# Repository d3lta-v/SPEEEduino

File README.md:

Designed by MakerFoundry LLP | Designed, assembled and tested in Singapore

# SPEEEduino
SPEEEduino is an easy to use Wi-Fi enabled microcontroller, designed and fabricated by EEE students. Users can write programs to connect or control things over the Internet.

Official Reference Website: [https://sites.google.com/view/speeeduino/home](https://sites.google.com/view/speeeduino/home)

Related project: [ESPblaster](https://github.com/sammy0025/ESPblaster)

## Technical information

### Repository Layout
* **SPEEEduino_v1.0**: EAGLE files for the old SPEEEduino v1.0, which is deprecated
* **SPEEEduino_v1.1**: EAGLE files for thew new SPEEEduino
* **Low Level Library**: The SPEEEduino Low Level Library, which is an Arduino library that provides an easy way to interface with the ESP8266-01 module with the SPEEEduino.
* **docs**: The [github.io homepage](https://sammy0025.github.io/SPEEEduino/) for the SPEEEduino
* **Image Assets**: Image assets for websites related to the SPEEEduino and markdown pages.

### Startup states table
A simplified version of this table is also available on the back of the SPEEEduino v1.1's board.

|  | GPIO0 (1) | GPIO2 (2) | ESP-RX connect to D4 (3) | ESP-TX connect to D2 (4) | ESP-RESET Button |
|---------|:---------:|:---------:|:---------:|:---------:|:---------:|
| Wi-Fi Enable | ⬆️ | ⬆️ | ⬆️ | ⬆️ | Leave open |
| Disconnect ESP-01 | ❎ | ❎ | ⬇️ | ⬇️ | Leave open |
| Reset ESP-01 | ❎ | ❎ | ❎ | ❎ | Press down |
| Flash ESP-01 | ⬇️ | ⬆️ | ⬇️ | ⬇️ | Press down, set switches, release |

## Contributing
Contributing to the SPEEEduino Git Repository requires you to have EAGLE 8.4 or newer which supports Managed Libraries.

SPEEEduino primarily uses EAGLE's Managed Libraries made by Sparkfun, but also contain our own custom footprints and SMD component footprints from Cytron.

## Our team
* Project Supervisor: [Teo Shin Jen](https://www.youracclaim.com/user/sjteo)
* Chief Designer: Pan Ziyue ([@sammy0025](https://twitter.com/sammy0025))
* Assistants/Advisers: Julian Kang ([@Julian_KBK](https://twitter.com/Julian_KBK)), Goh Qian Zhe ([@QianZheGoh](https://twitter.com/QianZheGoh))
* Videographer: [@QianZheGoh](https://twitter.com/QianZheGoh)
* The awesome folks at Arduino, Sparkfun and Adafruit for technical reference and ECAD models.

Open Source Hardware (OSHW)

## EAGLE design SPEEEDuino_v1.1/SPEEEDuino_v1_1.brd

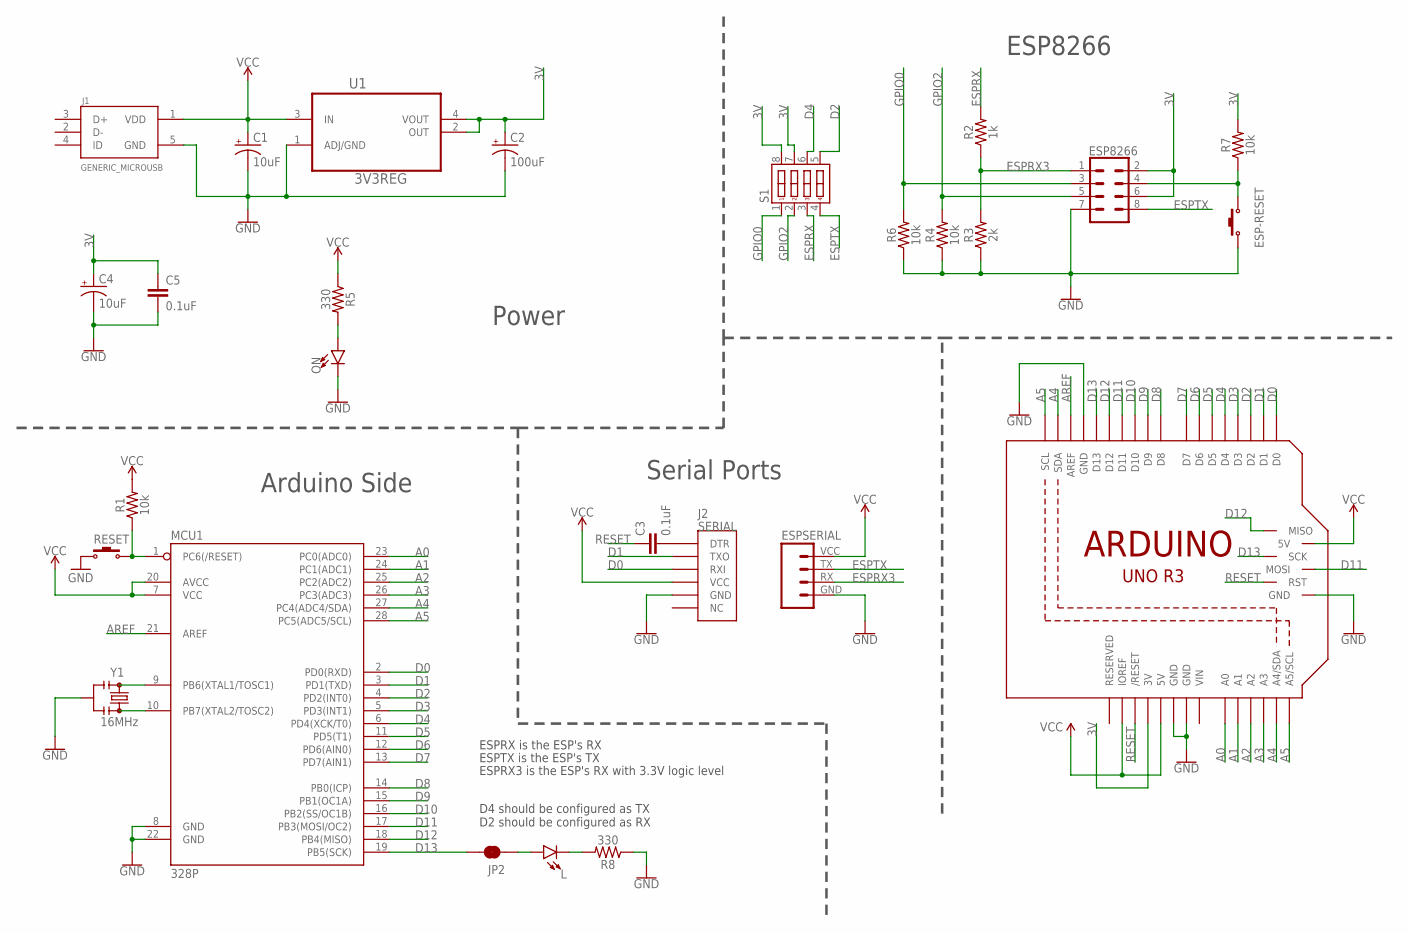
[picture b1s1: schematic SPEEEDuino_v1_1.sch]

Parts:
C1: 10uF; EIA3528
C2: 100uF; PANASONIC_D
C3, C5: 0.1uF; 1206
C4: 10uF; EIA3216
ESP8266: CONN_04X2; 2X4
ESP-RESET: SW-PB_(KAN0641); S-SP-4N-KAN0641
ESPSERIAL: ESP8266-SERIAL0; 1X04
J1: GENERIC_MICROUSB; FRAMATOME_10118194-0001LF
J2: SERIAL; CP2102_DEVICE_SIDE
JP2: JUMPER-SMT_2_NC_TRACE_SILK; SMT-JUMPER_2_NC_TRACE_SILK
L: LED3MM; LED_3MM
M1: ARDUINO_R3_ICSP; ARDUINOR3_ICSP
MCU1: 328P; DIP28
ON: LED3MM; LED_3MM
R1, R4, R6, R7: 10k; 1206
R2: 1k; 1206
R3: 2k; 1206
R5, R8: 330; 1206
RESET: SW-PB_(KAN0641); S-SP-4N-KAN0641
S1: 4 WAYS; SW-DIP-4-SMD
U1: 3V3REG; SOT230P696X180-4N
Y1: 16MHz; RESONATOR-SMD-3.2X1.3

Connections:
3V: C2.+, C4.+, C5.1, ESP8266.2, ESP8266.6, M1.3V, R7.2, S1.7, S1.8, U1.2 (OUT), U1.4 (VOUT)
A0: M1.A0, MCU1.23 (PC0(ADC0))
A1: M1.A1, MCU1.24 (PC1(ADC1))
A2: M1.A2, MCU1.25 (PC2(ADC2))
A3: M1.A3, MCU1.26 (PC3(ADC3))
A4: M1.A4 (A4/SDA), M1.SDA, MCU1.27 (PC4(ADC4/SDA))
A5: M1.A5 (A5/SCL), M1.SCL, MCU1.28 (PC5(ADC5/SCL))
AREF: M1.AREF, MCU1.21 (AREF)
D0: J2.P$3 (RXI), M1.D0, MCU1.2 (PD0(RXD))
D1: J2.P$2 (TXO), M1.D1, MCU1.3 (PD1(TXD))
D2: M1.D2, MCU1.4 (PD2(INT0)), S1.5
D3: M1.D3, MCU1.5 (PD3(INT1))
D4: M1.D4, MCU1.6 (PD4(XCK/T0)), S1.6
D5: M1.D5, MCU1.11 (PD5(T1))
D6: M1.D6, MCU1.12 (PD6(AIN0))
D7: M1.D7, MCU1.13 (PD7(AIN1))
D8: M1.D8, MCU1.14 (PB0(ICP))
D9: M1.D9, MCU1.15 (PB1(OC1A))
D10: M1.D10, MCU1.16 (PB2(SS/OC1B))
D11: M1.D11, M1.MOSI, MCU1.17 (PB3(MOSI/OC2))
D12: M1.D12, M1.MISO, MCU1.18 (PB4(MISO))
D13: JP2.2, M1.D13, M1.SCK, MCU1.19 (PB5(SCK))
DTR: C3.2, J2.P$1 (DTR)
ESPRESET: ESP8266.4, ESP-RESET.3 (2), ESP-RESET.4 (2), R7.1
ESPRX: R2.2, S1.3
ESPRX3: ESP8266.1, ESPSERIAL.RX (TX), R2.1, R3.2
ESPTX: ESP8266.8, ESPSERIAL.TX (RX), S1.4
GND: C1.C (-), C2.-, C4.-, C5.2, ESP8266.7, ESP-RESET.1, ESP-RESET.2 (1), ESPSERIAL.GND (VCC), J1.5 (GND), J2.P$5 (GND), M1.GND, M1.GND@1 (GND), M1.GND@2 (GND), M1.GND@3 (GND), MCU1.8 (GND), MCU1.22 (GND), ON.K (C), R3.1, R4.1, R6.1, R8.1, RESET.1, RESET.2 (1), U1.1 (ADJ/GND), Y1.2
GPIO0: ESP8266.3, R6.2, S1.1
GPIO2: ESP8266.5, R4.2, S1.2
unnamed: MCU1.10 (PB7(XTAL2/TOSC2)), Y1.3
unnamed: L.K (C), R8.2
unnamed: JP2.1, L.A
unnamed: ON.A, R5.2
unnamed: MCU1.9 (PB6(XTAL1/TOSC1)), Y1.1
RESET: C3.1, M1.RESET (/RESET), M1.RESET_ICSP (RST), MCU1.1 (PC6(/RESET)), R1.1, RESET.3 (2), RESET.4 (2)
VCC: C1.A (+), ESPSERIAL.VCC (GND), J1.1 (VDD), J2.P$4 (VCC), M1.5V, M1.5V_ICSP (5V), M1.IOREF, MCU1.7 (VCC), MCU1.20 (AVCC), R1.2, R5.1, U1.3 (IN)
VIN: M1.VIN

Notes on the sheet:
ESPRX is the ESP's RX
ESPTX is the ESP's TX
D4 should be configured as TX D2 should be configured as RX
ESPRX3 is the ESP's RX with 3.3V logic level
Power
Arduino Side
Serial Ports
ESP8266

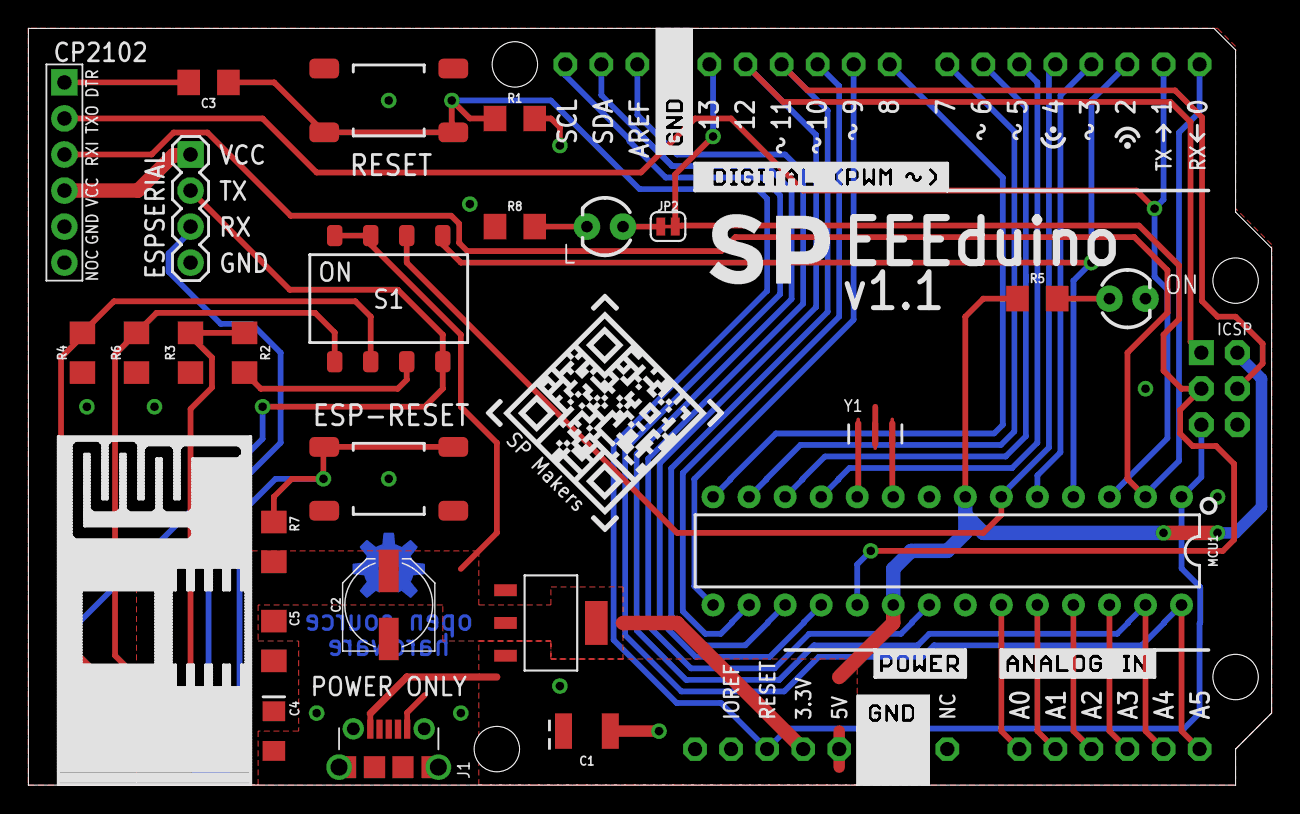
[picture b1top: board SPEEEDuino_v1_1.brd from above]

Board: 2 copper layers, 87.6 x 53.3 mm, 33 parts (0 on the bottom side), 37 nets.

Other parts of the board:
U$1: ESP8266-NEGASILK
U$2: SP-LOGO-BIGGER
U$3: ESP8266-NEGASILK-INV
U$4: OSHW-LOGO-M_COPPER-SOLDERMASK-INV
U$5: MAKERCLUB-QR
U$6: SP-LOGO-SMALL-INV

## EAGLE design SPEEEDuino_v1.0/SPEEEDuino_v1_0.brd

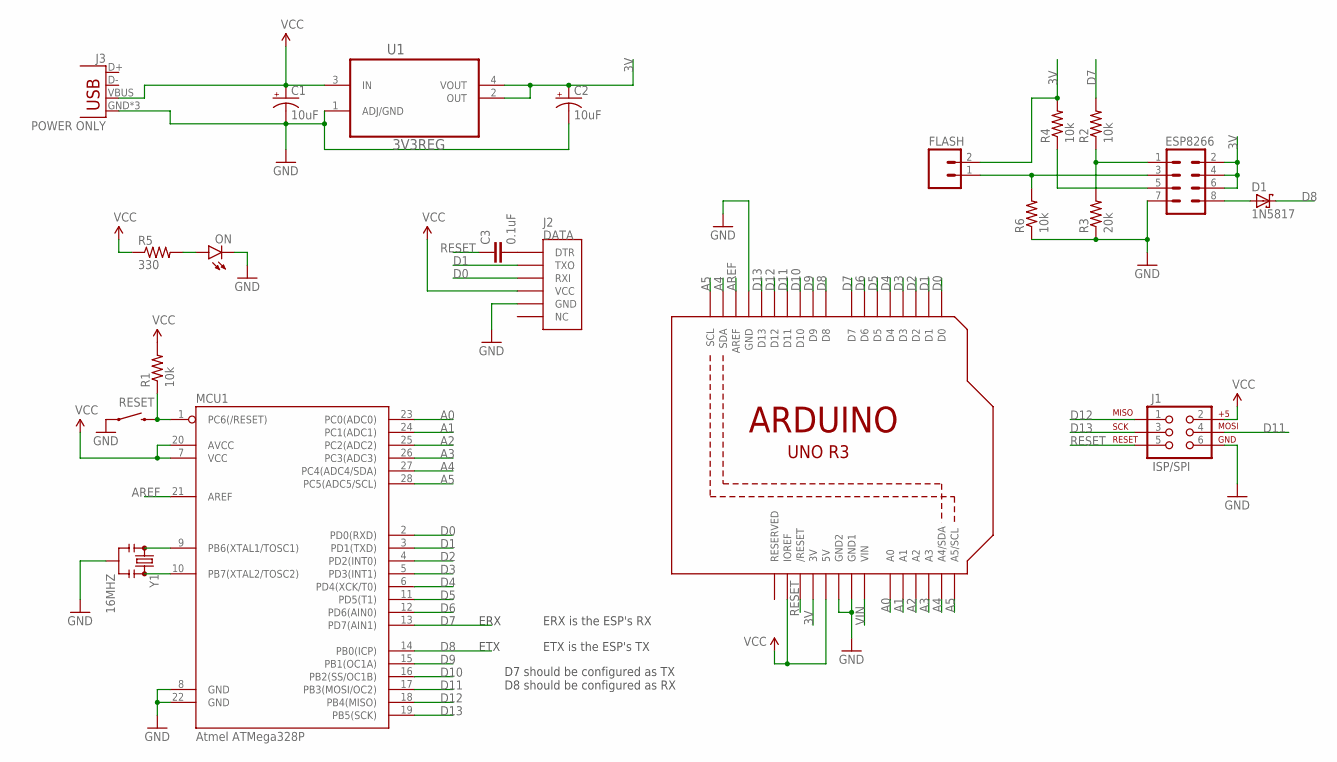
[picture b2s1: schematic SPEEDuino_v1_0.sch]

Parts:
C1, C2: 10uF; EIA3216-KIT
C3: 0.1uF; 1206
D1: 1N5817; DO41-10
ESP8266: M04X2; 2X4
FLASH: M02LOCK; 1X02_LOCK
J1: ISP/SPI; 2X3
J2: DATA; CP2102_DEVICE_SIDE
J3: POWER ONLY; USB-MICROB
MCU1: Atmel ATMega328P; DIL28-3
ON: LED3MM
R1, R2, R4, R6: 10k; 1206
R3: 20k; 1206
R5: 330; 1206
RESET: SWITCH-MOMENTARY-2PTH; TACTILE-PTH
U1: 3V3REG; SOT230P696X180-4N
U2: ARDUINOR3-DIMENSION; ARDUINOR3
Y1: 16MHZ; RESONATOR-SMD

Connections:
3V: C2.A (+), ESP8266.2, ESP8266.4, ESP8266.6, FLASH.2, R4.2, U1.2 (OUT), U1.4 (VOUT), U2.3V
A0: MCU1.23 (PC0(ADC0)), U2.A0
A1: MCU1.24 (PC1(ADC1)), U2.A1
A2: MCU1.25 (PC2(ADC2)), U2.A2
A3: MCU1.26 (PC3(ADC3)), U2.A3
A4: MCU1.27 (PC4(ADC4/SDA)), U2.A4 (A4/SDA), U2.SDA
A5: MCU1.28 (PC5(ADC5/SCL)), U2.A5 (A5/SCL), U2.SCL
AREF: MCU1.21 (AREF), U2.AREF
D0: J2.P$3 (RXI), MCU1.2 (PD0(RXD)), U2.D0
D1: J2.P$2 (TXO), MCU1.3 (PD1(TXD)), U2.D1
D2: MCU1.4 (PD2(INT0)), U2.D2
D3: MCU1.5 (PD3(INT1)), U2.D3
D4: MCU1.6 (PD4(XCK/T0)), U2.D4
D5: MCU1.11 (PD5(T1)), U2.D5
D6: MCU1.12 (PD6(AIN0)), U2.D6
D7: MCU1.13 (PD7(AIN1)), R2.2, U2.D7
D8: D1.C, MCU1.14 (PB0(ICP)), U2.D8
D9: MCU1.15 (PB1(OC1A)), U2.D9
D10: MCU1.16 (PB2(SS/OC1B)), U2.D10
D11: J1.4, MCU1.17 (PB3(MOSI/OC2)), U2.D11
D12: J1.1, MCU1.18 (PB4(MISO)), U2.D12
D13: J1.3, MCU1.19 (PB5(SCK)), U2.D13
GND: C1.C (-), C2.C (-), ESP8266.7, J1.6, J2.P$5 (GND), J3.GND, J3.MT1 (GND), J3.MT2 (GND), MCU1.8 (GND), MCU1.22 (GND), ON.K (C), R3.1, R6.1, RESET.1, U1.1 (ADJ/GND), U2.GND, U2.GND1, U2.GND2, Y1.2
unnamed: MCU1.10 (PB7(XTAL2/TOSC2)), Y1.3
unnamed: ESP8266.1, R2.1, R3.2
unnamed: ESP8266.5, R4.1
unnamed: ON.A, R5.2
unnamed: MCU1.9 (PB6(XTAL1/TOSC1)), Y1.1
unnamed: C3.2, J2.P$1 (DTR)
unnamed: D1.A, ESP8266.8
unnamed: ESP8266.3, FLASH.1, R6.2
RESET: C3.1, J1.5, MCU1.1 (PC6(/RESET)), R1.1, RESET.3 (2), U2.RESET (/RESET)
VCC: C1.A (+), J1.2, J2.P$4 (VCC), J3.VBUS, MCU1.7 (VCC), MCU1.20 (AVCC), R1.2, R5.1, U1.3 (IN), U2.5V, U2.IOREF
VIN: U2.VIN

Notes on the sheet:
ERX
ETX
ERX is the ESP's RX
ETX is the ESP's TX
D7 should be configured as TX D8 should be configured as RX

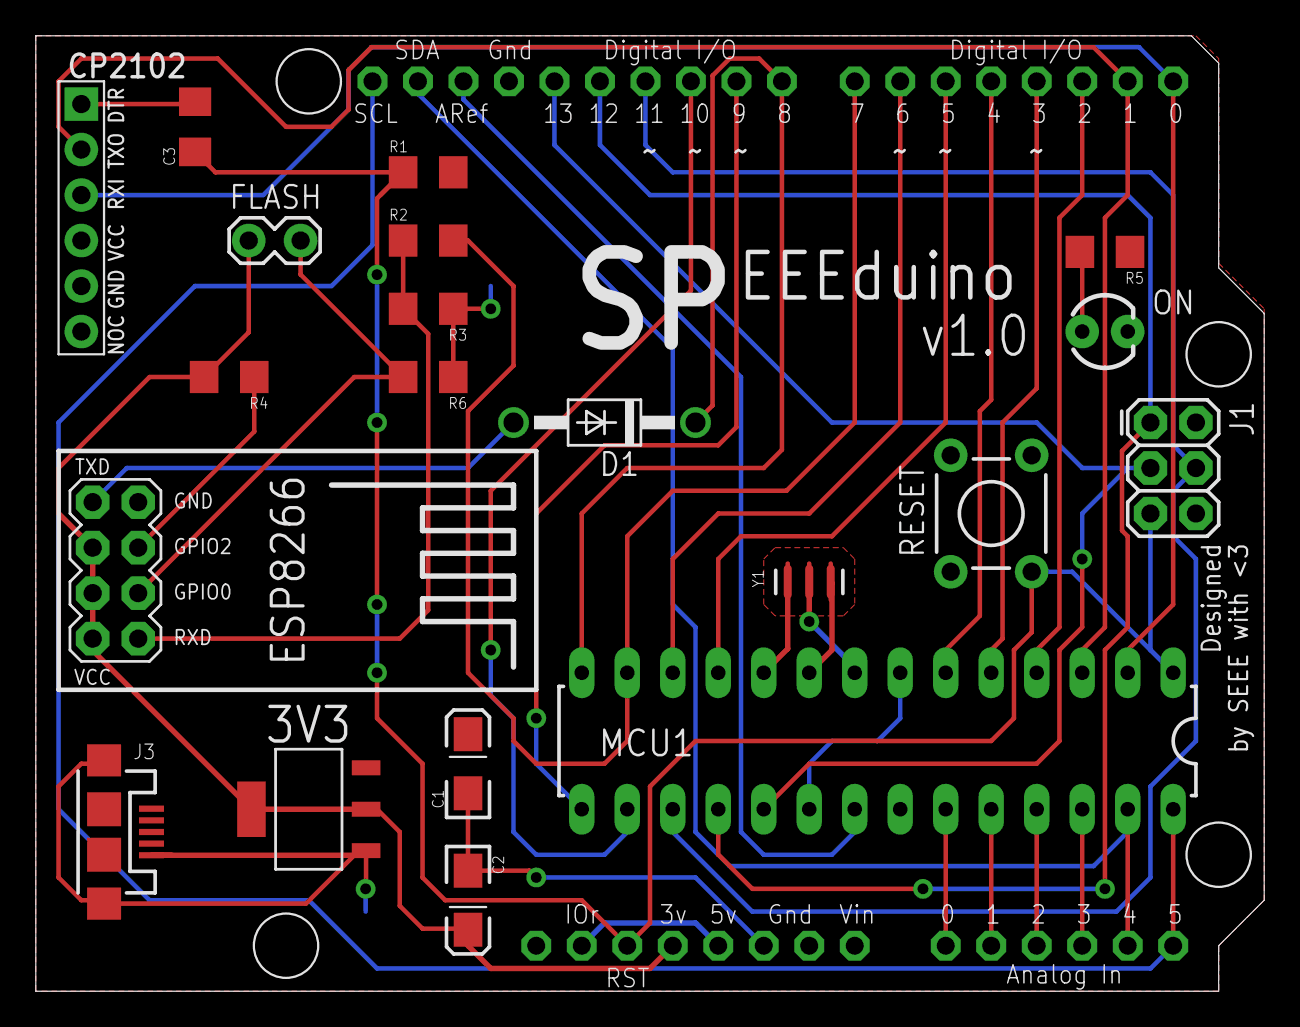
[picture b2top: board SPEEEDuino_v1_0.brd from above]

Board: 2 copper layers, 68.6 x 53.3 mm, 21 parts (0 on the bottom side), 33 nets.

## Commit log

2017-06-06 added populated PCB preview
2017-06-06 added populated board to README
2017-06-06 slightly modified PCB preview
2017-06-12 Added documentation using Github Sites, do not use docs for now
2017-06-12 Added the noob guide to Arduino and SPEEEduino
2017-06-12 Edited index.md for docs to delete default info
2017-06-12 Added front matter to index.md
2017-06-12 Added incomplete page-header.html
2017-06-12 Modified config.yml to the full version
2017-06-12 Added custom layout foundations
2017-06-12 Changed default to the full Github default
2017-06-14 Edited default Github Page and index.md
2017-06-15 Added image of v1.0 populated
2017-06-24 Changed silkscreen text sizes on 1.1, added more documentation in docs
2017-06-24 Added photos for documentation
2017-06-24 Added Arduino IDE documentation pictures
2017-06-24 Added blink demonstration for Arduino IDE
2017-06-24 Cropped screenshots from Arduino IDE
2017-06-24 Edited CP2102 documentation image
2017-06-25 Edited Github Pages to use proper formatting
2017-06-25 cleaned up layout problem on Github Pages
2017-06-25 changed __layouts to _layouts
2017-06-25 Changed some configurations for better Github Pages to work
2017-06-25 Added title to new Github Pages index.md
2017-06-25 edited webpage title to prevent character conflict
2017-06-25 Added back the title on index.md
2017-06-25 removed title as it causes index.md to not render properly
2017-06-25 modified the ESP01_Onboard documentation picture
2017-06-25 test commit for pages
2017-07-11 Added the SPEEEduino Low Level Library that uses embedXcode, with a full embedXcode project
2017-07-11 Added all keywords into the keywords.txt
2017-07-11 Slightly altered method names to Arduino's API styles guide
2017-07-17 Modified LLLibrary, but do not use for now
2017-07-20 Added data receiving capabilities, +IPD inputs now can be parsed into a String, but it must not exceed 1024 bytes
2017-07-22 Improved receiveData() method, added keywords to keywords.txt, added functions to set SoftAP settings, begin TCP server
2017-07-22 Updated README.md and github.io homepage markdown file
2017-08-03 Improved receive data functionality
2017-08-03 Deleted front matter on docs to re-render the Github Pages index.md
2017-08-03 Added theme back
2017-08-03 Added default.html in Github Pages
2017-08-03 Got rid of theme specification in config.yml
2017-09-13 Added fully functional multiple connection mode data sending, and optimised more code with C-equivalents
2017-09-13 Added example code
2017-09-13 Edited keywords.txt
2017-09-13 Added Low Level Library installable zip file
2017-09-13 Renamed low level library to allow Arduino IDE installation
2017-09-13 Removed scss assets due to page build failure
2017-09-13 added assets back
2017-09-13 Added sass assets to Github Pages
2017-09-13 New Gerber files for larger silkscreen text
2017-09-14 Added IR sensor code example
2017-09-24 Optimised some memory for the SPEEEduino low level library
2017-10-17 Added ParkLamp example
2017-10-17 Updated library zip file
2017-10-18 Improved ParkLamp.ino example to include on/off state
2017-10-19 Deleted deprecated library
2017-10-20 Added static IP setting function, but keep in mind it has not been tested
2017-10-20 Updated low level library build
2017-10-20 Updated examples to comment out DHCP enabling to prevent weird bug
2017-10-20 Updated low level library zip file with new examples
2017-10-21 Fixed minor bug with static IP on the low level library
2017-10-25 Added autogenerated documentation
2017-10-25 Added documentation link to homepage
2017-10-25 deleted readme
2017-10-26 Added @brief to all headerdoc documentations
2017-10-28 Updated v1.1 schematics and board to use Sparkfun's Managed libraries
2017-10-28 Deleted xcuserstate to prevent committing useless data
2017-10-28 Added more relevant gitignore entries
2017-10-28 Updated README to reflect contribution requirements
2018-07-12 fixed readme table

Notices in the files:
parts and their libraries:
SparkFun-Aesthetics: Licensing: Creative Commons ShareAlike 4.0 International - https://creativecommons.org/licenses/by-sa/4.0
